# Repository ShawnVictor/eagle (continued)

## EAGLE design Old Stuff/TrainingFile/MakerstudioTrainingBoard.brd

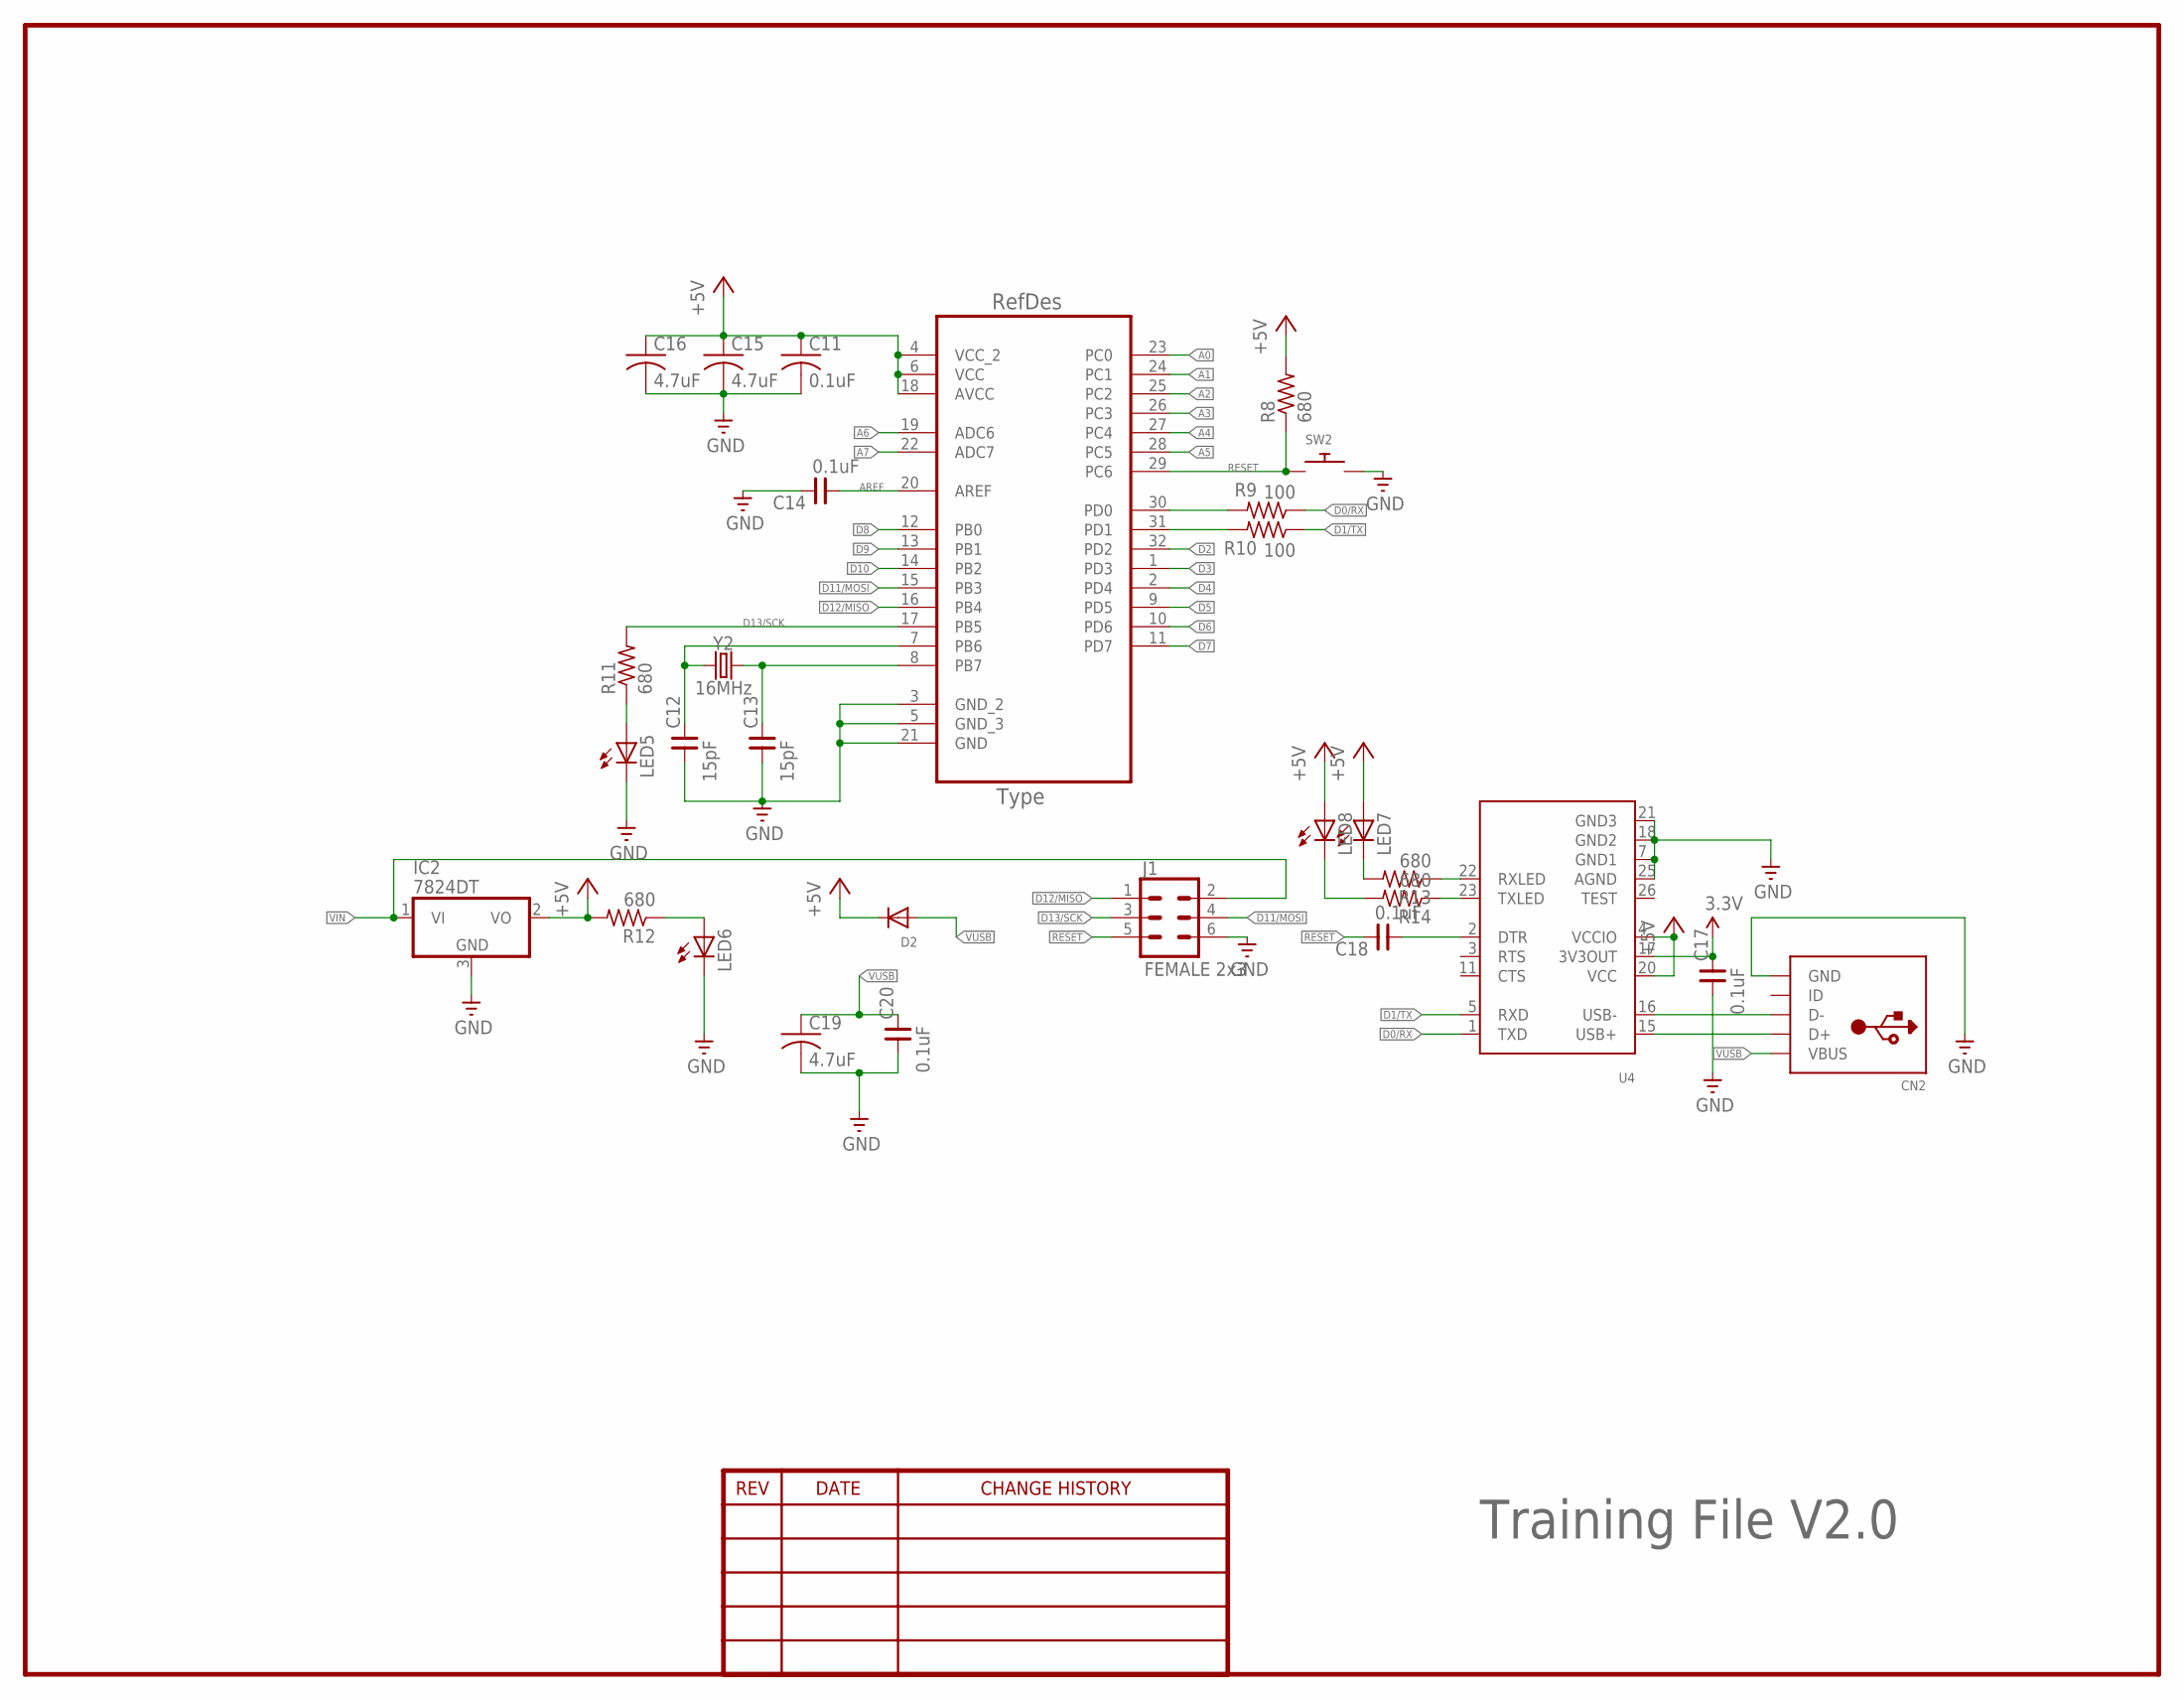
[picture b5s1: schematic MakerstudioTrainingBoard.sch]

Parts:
C11: 0.1uF; C0805
C12, C13: 15pF; 0805
C14, C17, C18, C20: 0.1uF; 0805
C15, C16, C19: 4.7uF; C0805
CN2: USBMINIB; USB-MINIB
D2: DIODESOD-123; SOD-123
IC2: 7824DT; TO252
J1: FEMALE 2x3; 2X3
LED5, LED6, LED7, LED8: LEDCHIPLED_0805; CHIPLED_0805
R8, R11, R12, R13, R14: 680; R0805
R9, R10: 100; R0805
SW2: SWITCH_PUSHBUTTONEVQ-PE; TACT_PANA-EVQ
U3: ATMEGA328P-AU; QFP80P900X900X120-32N
U4: FT232RLSSOP28; SSOP28DB
Y2: 16MHz; HC49US

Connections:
3.3V: C17.2, U4.17 (3V3OUT)
+5V: C11.1, C15.1, C16.1, D2.C, IC2.2 (VO), LED7.A, LED8.A, R8.2, R12.2, U3.4 (VCC_2), U3.6 (VCC), U3.18 (AVCC), U4.4 (VCCIO), U4.20 (VCC)
A0: U3.23 (PC0)
A1: U3.24 (PC1)
A2: U3.25 (PC2)
A3: U3.26 (PC3)
A4: U3.27 (PC4)
A5: U3.28 (PC5)
A6: U3.19 (ADC6)
A7: U3.22 (ADC7)
AREF: C14.1, U3.20 (AREF)
D0/RX: R9.1, U4.1 (TXD)
D1/TX: R10.1, U4.5 (RXD)
D2: U3.32 (PD2)
D3: U3.1 (PD3)
D4: U3.2 (PD4)
D5: U3.9 (PD5)
D6: U3.10 (PD6)
D7: U3.11 (PD7)
D8: U3.12 (PB0)
D9: U3.13 (PB1)
D10: U3.14 (PB2)
D11/MOSI: J1.4, U3.15 (PB3)
D12/MISO: J1.1, U3.16 (PB4)
D13/SCK: J1.3, R11.2, U3.17 (PB5)
GND: C11.2, C12.1, C13.1, C14.2, C15.2, C16.2, C17.1, C19.2, C20.1, CN2.GND, IC2.3 (GND), J1.6, LED5.C, LED6.C, SW2.P$2, U3.3 (GND_2), U3.5 (GND_3), U3.21 (GND), U4.7 (GND1), U4.18 (GND2), U4.21 (GND3), U4.25 (AGND)
unnamed: LED5.A, R11.1
unnamed: C13.2, U3.8 (PB7), Y2.2
unnamed: C12.2, U3.7 (PB6), Y2.1
unnamed: R9.2, U3.30 (PD0)
unnamed: R10.2, U3.31 (PD1)
unnamed: LED6.A, R12.1
unnamed: CN2.D+, U4.15 (USB+)
unnamed: CN2.D-, U4.16 (USB-)
unnamed: R13.1, U4.22 (RXLED)
unnamed: R14.1, U4.23 (TXLED)
unnamed: LED8.C, R14.2
unnamed: LED7.C, R13.2
unnamed: C18.1, U4.2 (DTR)
RESET: C18.2, J1.5, R8.1, SW2.P$1, U3.29 (PC6)
VIN: IC2.1 (VI), J1.2
VUSB: C19.1, C20.2, CN2.VBUS, D2.A

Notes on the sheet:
Training File V2.0

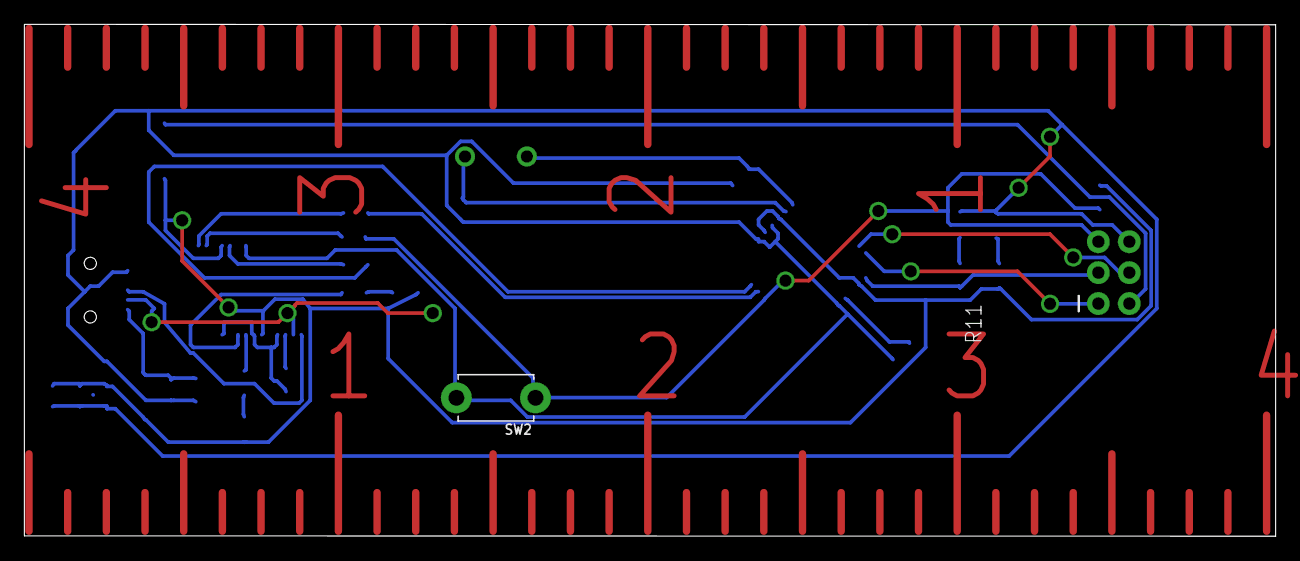
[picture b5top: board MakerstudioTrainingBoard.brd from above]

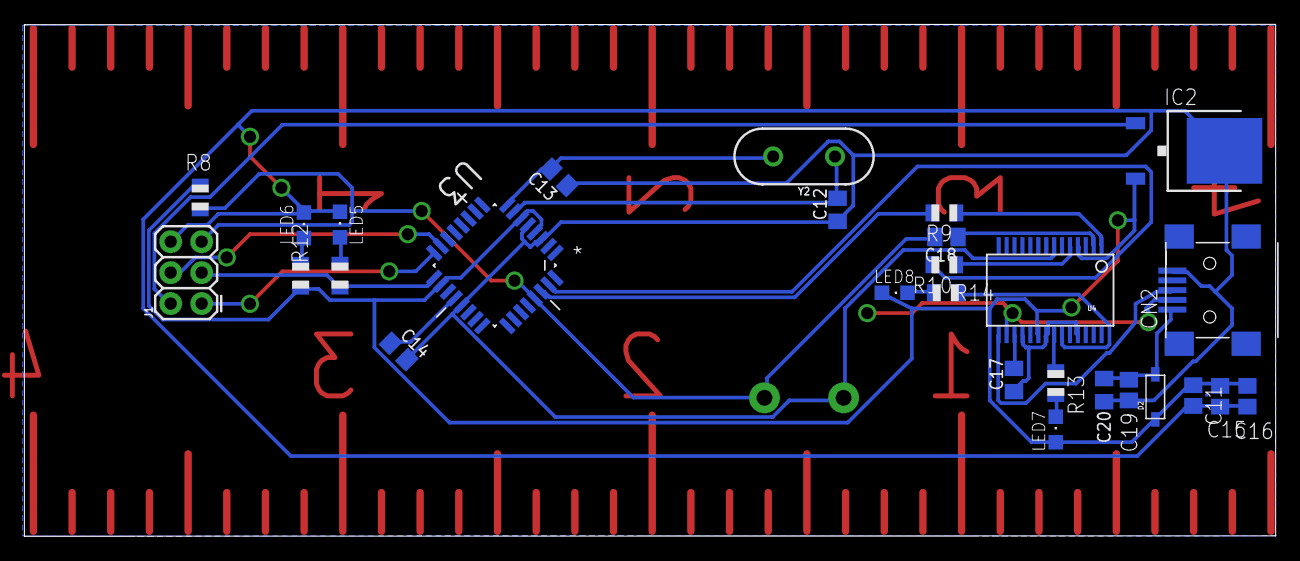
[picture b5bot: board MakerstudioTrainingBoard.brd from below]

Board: 2 copper layers, 102.7 x 42.0 mm, 29 parts (28 on the bottom side), 25 nets.

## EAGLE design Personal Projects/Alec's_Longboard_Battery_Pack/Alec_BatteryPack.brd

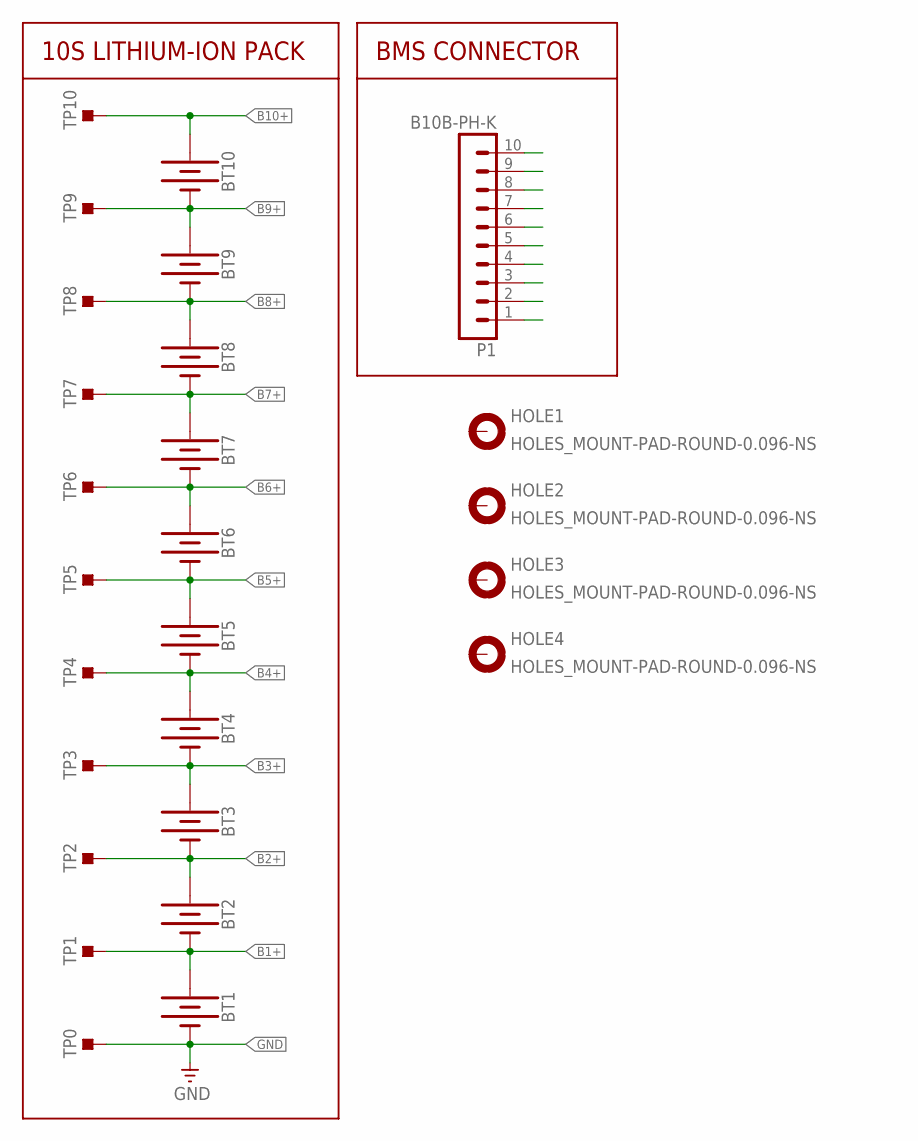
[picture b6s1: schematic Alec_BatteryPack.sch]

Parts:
BT1, BT2, BT3, BT4, BT5, BT6, BT7, BT8, BT9, BT10: BATTERY-18650; BATTERY_18650-HOLDER
HOLE1, HOLE2, HOLE3, HOLE4: HOLES_MOUNT-PAD-ROUND-0.096-NS; HOLES_096-PAD-NS
P1: B10B-PH-K
TP0, TP1, TP2, TP3, TP4, TP5, TP6, TP7, TP8, TP9, TP10: TESTPOINT_TPS-SMD-10SN; TESTPOINT_SMD-10SN

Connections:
B1+: BT1.PWR@1 (+), BT2.GND@1 (-), TP1.TP
B2+: BT2.PWR@1 (+), BT3.GND@1 (-), TP2.TP
B3+: BT3.PWR@1 (+), BT4.GND@1 (-), TP3.TP
B4+: BT4.PWR@1 (+), BT5.GND@1 (-), TP4.TP
B5+: BT5.PWR@1 (+), BT6.GND@1 (-), TP5.TP
B6+: BT6.PWR@1 (+), BT7.GND@1 (-), TP6.TP
B7+: BT7.PWR@1 (+), BT8.GND@1 (-), TP7.TP
B8+: BT8.PWR@1 (+), BT9.GND@1 (-), TP8.TP
B9+: BT9.PWR@1 (+), BT10.GND@1 (-), TP9.TP
B10+: BT10.PWR@1 (+), TP10.TP
GND: BT1.GND@1 (-), TP0.TP

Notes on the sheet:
10S LITHIUM-ION PACK
BMS CONNECTOR

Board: 2 copper layers, 26 parts (0 on the bottom side), 11 nets, no tracks yet.

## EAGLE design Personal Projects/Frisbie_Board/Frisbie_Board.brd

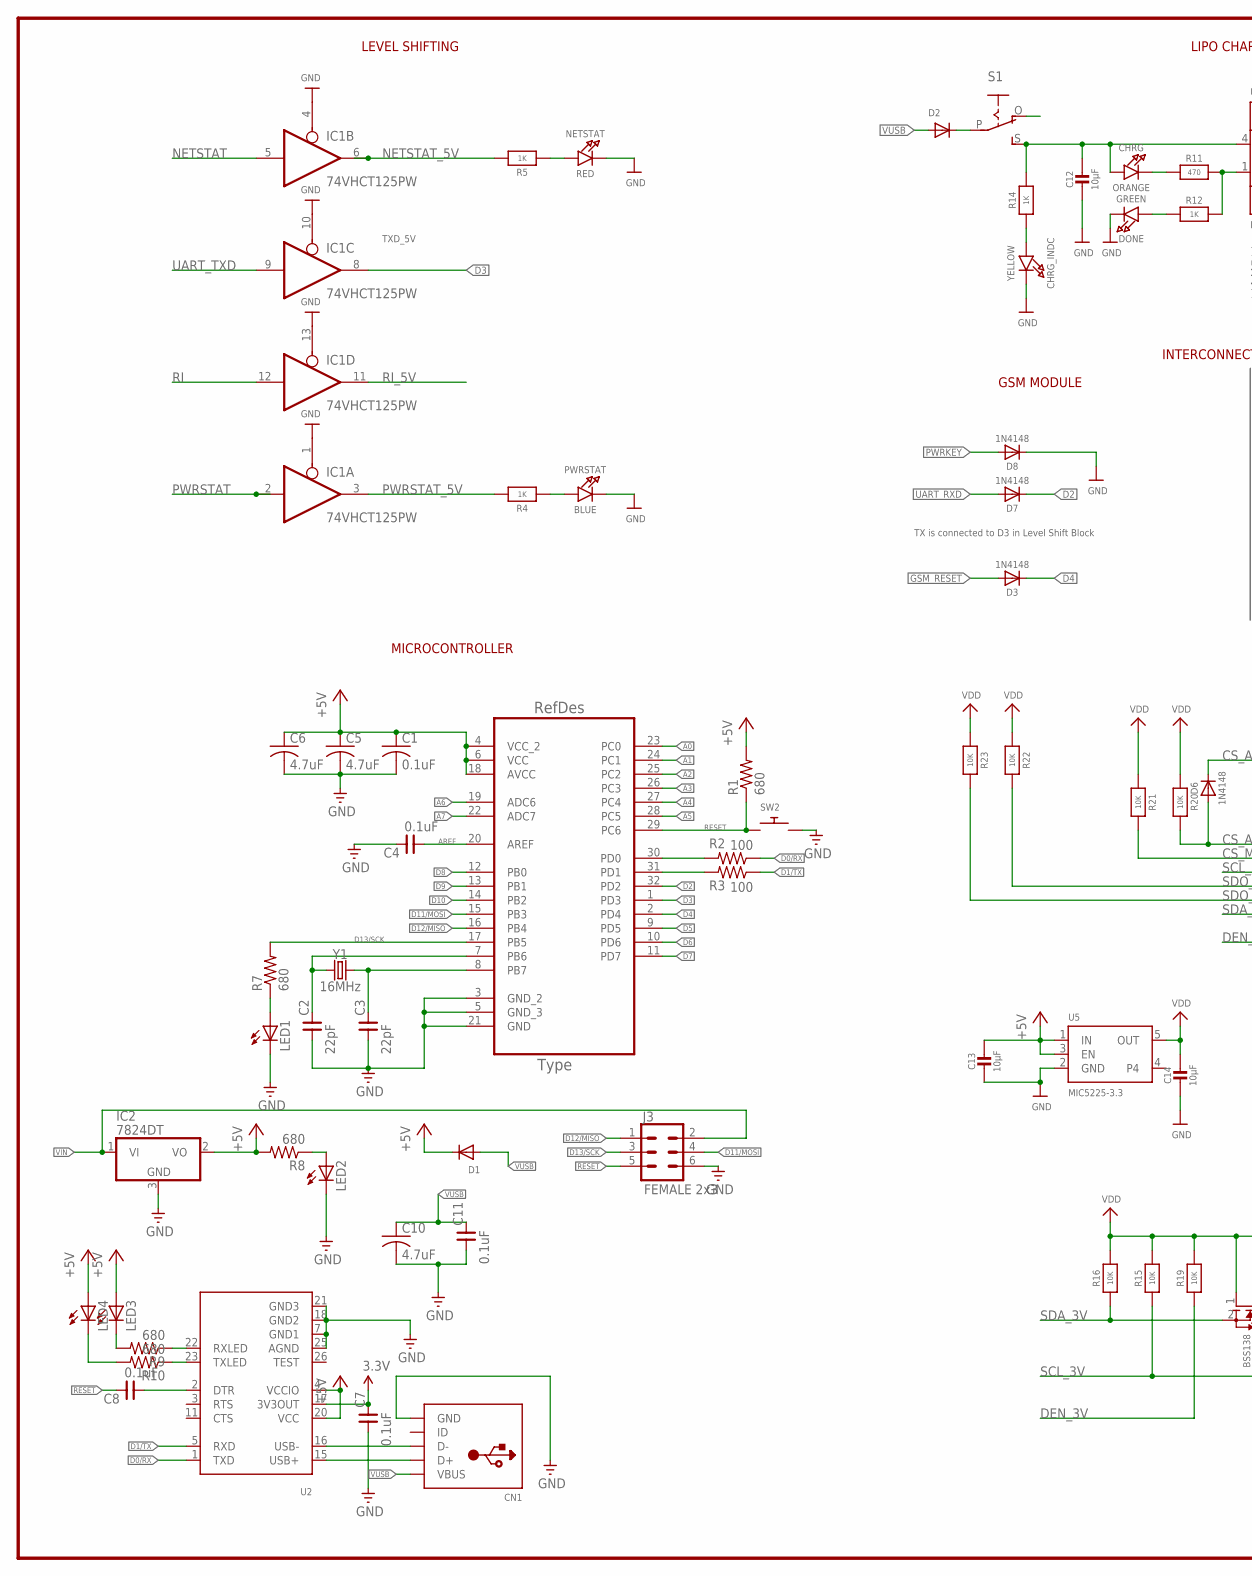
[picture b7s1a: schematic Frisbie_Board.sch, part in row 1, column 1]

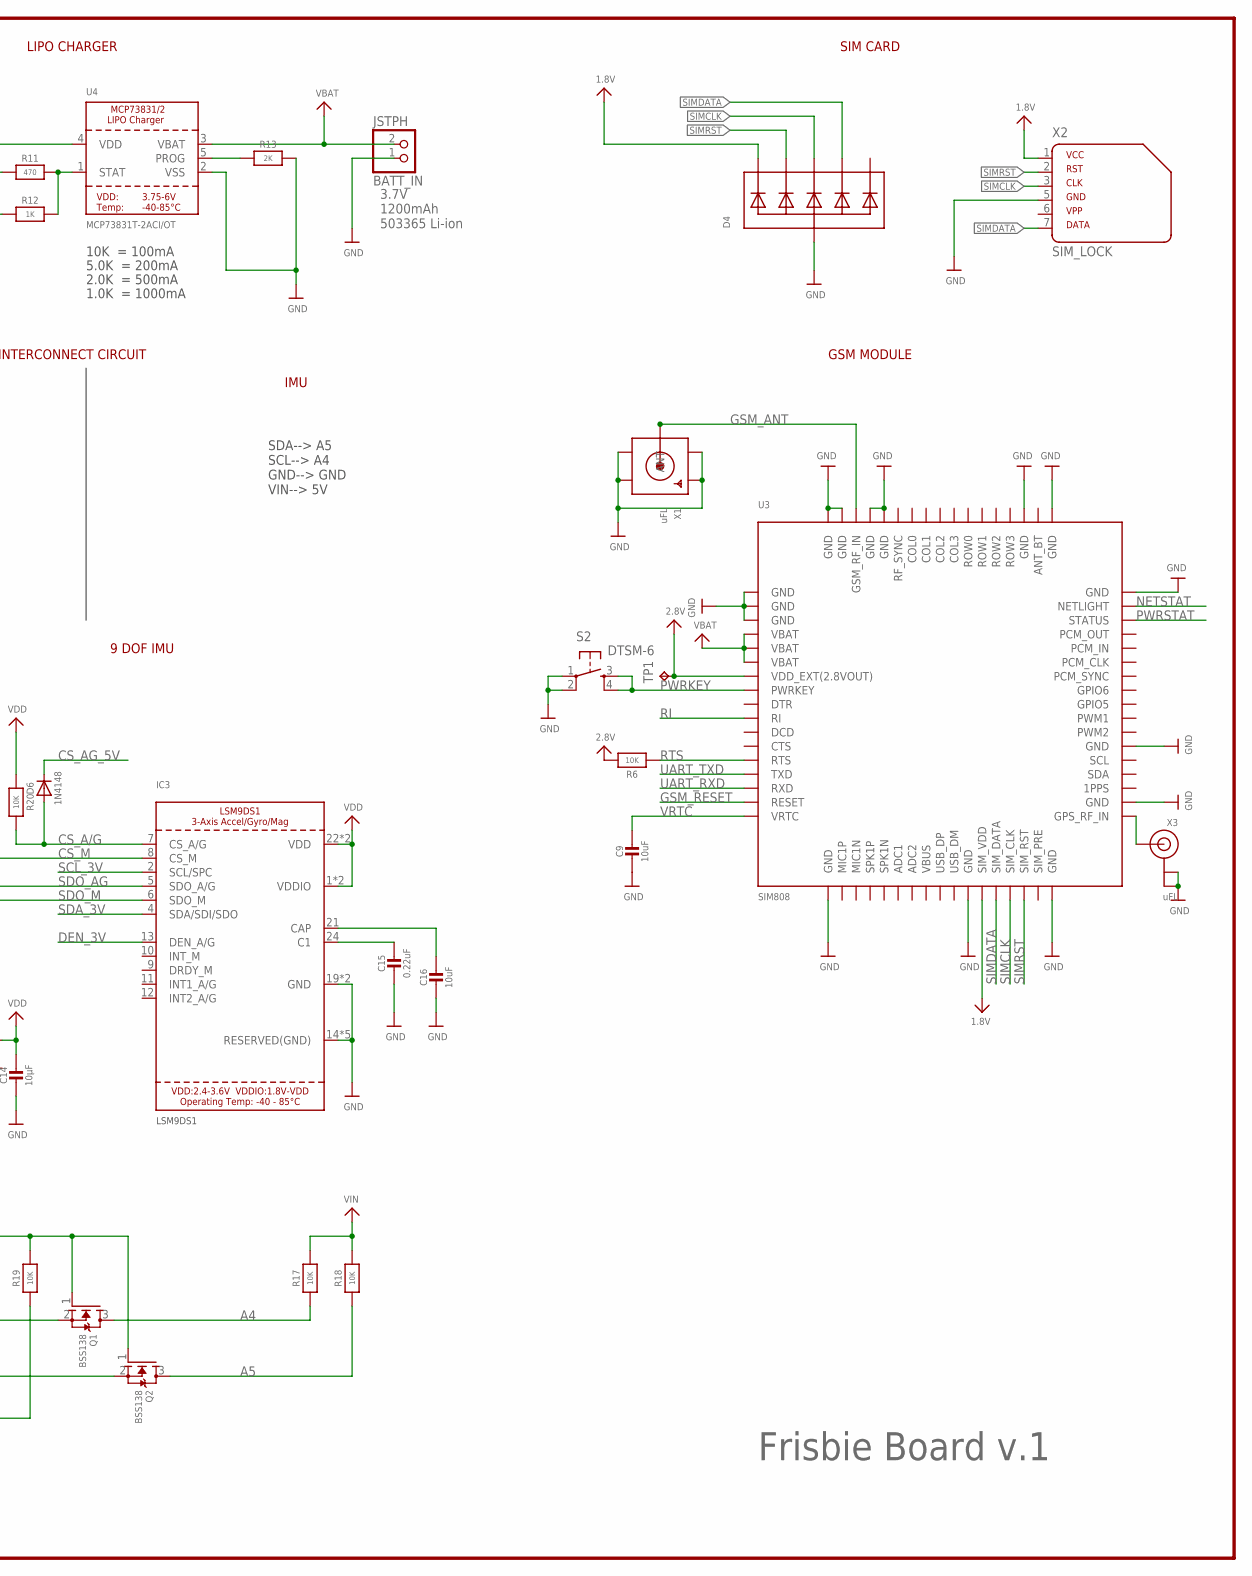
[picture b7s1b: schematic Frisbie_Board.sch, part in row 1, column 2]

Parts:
BATT_IN: JSTPH; JSTPH2
C1: 0.1uF; C0805
C2, C3: 22pF; 0805
C4, C7, C8, C11: 0.1uF; 0805
C5, C6, C10: 4.7uF; C0805
C9, C16: 10uF; 0805-NO
C12, C13, C14: 10µF; 0805-NO
C15: 0.22uF; 0805_10MGAP
CHRG: ORANGE; CHIPLED_0805_NOOUTLINE
CHRG_INDC: YELLOW; CHIPLED_0805_NOOUTLINE
CN1: USBMINIB; USB-MINIB
D1, D2: DIODESOD-123; SOD-123
D3, D6, D7, D8: 1N4148; SOD-323
D4: TVSARRAY_5LANE; SOT363
DONE: GREEN; CHIPLED_0805_NOOUTLINE
IC1: 74VHCT125PW; TSSOP14
IC2: 7824DT; TO252
IC3: LSM9DS1; LGA24_3.5X3.1MM
J3: FEMALE 2x3; 2X3
LED1, LED2, LED3, LED4: LEDCHIPLED_0805; CHIPLED_0805
NETSTAT: RED; CHIPLED_0805_NOOUTLINE
PWRSTAT: BLUE; CHIPLED_0805_NOOUTLINE
Q1, Q2: BSS138; SOT23-WIDE
R1, R7, R8, R9, R10: 680; R0805
R2, R3: 100; R0805
R4, R5, R12, R14: 1K; 0805-NO
R6, R15, R17, R18, R19, R20, R21, R23: 10K; 0805-NO
R11: 470; 0805-NO
R13: 2K; 0805-NO
R16, R22: 10K; 0805_10MGAP
S1: EG1218S; EG1218
S2: DTSM-6
SW2: SWITCH_PUSHBUTTONEVQ-PE; TACT_PANA-EVQ
TP1: TPTP11R; TP11R
U1: ATMEGA328P-AU; QFP80P900X900X120-32N
U2: FT232RLSSOP28; SSOP28DB
U3: SIM808; SIM900_SMT
U4: MCP73831T-2ACI/OT; SOT23-5
U5: MIC5225-3.3; SOT23-5
X1: uFL; SMA_EDGELAUNCH_UFL
X2: SIM_LOCK; SIM_5002
X3: uFL; U.FL
Y1: 16MHz; HC49US

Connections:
1.8V: D4.1 (C1), U3.P$29 (SIM_VDD), X2.1
2.8V: R6.2, TP1.TP, U3.P$7 (VDD_EXT(2.8VOUT))
3.3V: C7.2, U2.17 (3V3OUT)
+5V: C1.1, C5.1, C6.1, C13.1, D1.C, IC2.2 (VO), LED3.A, LED4.A, R1.2, R8.2, U1.4 (VCC_2), U1.6 (VCC), U1.18 (AVCC), U2.4 (VCCIO), U2.20 (VCC), U5.1 (IN), U5.3 (EN)
A0: U1.23 (PC0)
A1: U1.24 (PC1)
A2: U1.25 (PC2)
A3: U1.26 (PC3)
A4: Q1.3 (D), R17.1, U1.27 (PC4)
A5: Q2.3 (D), R18.1, U1.28 (PC5)
A6: U1.19 (ADC6)
A7: U1.22 (ADC7)
AREF: C4.1, U1.20 (AREF)
C1: C15.1, IC3.24 (C1)
CAP: C16.1, IC3.21 (CAP)
CS_A/G: D6.A, IC3.7 (CS_A/G), R20.2
CS_AG_5V: D6.C
CS_M: IC3.8 (CS_M), R21.2
D0/RX: R2.1, U2.1 (TXD)
D1/TX: R3.1, U2.5 (RXD)
D2: D7.C, U1.32 (PD2)
D3: IC1.8 (O), U1.1 (PD3)
D4: D3.C, U1.2 (PD4)
D5: U1.9 (PD5)
D6: U1.10 (PD6)
D7: U1.11 (PD7)
D8: U1.12 (PB0)
D9: U1.13 (PB1)
D10: U1.14 (PB2)
D11/MOSI: J3.4, U1.15 (PB3)
D12/MISO: J3.1, U1.16 (PB4)
D13/SCK: J3.3, R7.2, U1.17 (PB5)
DEN_3V: IC3.13 (DEN_A/G), R19.1
GND: BATT_IN.1, C1.2, C2.1, C3.1, C4.2, C5.2, C6.2, C7.1, C9.2, C10.2, C11.1, C12.2, C13.2, C14.2, C15.2, C16.2, CHRG_INDC.C, CN1.GND, D4.2 (A), D8.C, DONE.C, IC1.1 (OE), IC1.4 (OE), IC1.7 (GND), IC1.10 (OE), IC1.13 (OE), IC2.3 (GND), IC3.14 (RESERVED(GND)), IC3.15 (RESERVED(GND)), IC3.16 (RESERVED(GND)), IC3.17 (RESERVED(GND)), IC3.18 (RESERVED(GND)), IC3.19 (GND), IC3.20 (GND), J3.6, LED1.C, LED2.C, NETSTAT.C, PWRSTAT.C, R13.2, S2.1, S2.2, SW2.P$2, U1.3 (GND_2), U1.5 (GND_3), U1.21 (GND), U2.7 (GND1), U2.18 (GND2), U2.21 (GND3), U2.25 (AGND), U3.P$1 (GND), U3.P$2 (GND), U3.P$3 (GND), U3.P$18 (GND), U3.P$28 (GND), U3.P$34 (GND), U3.P$36 (GND), U3.P$40 (GND), U3.P$51 (GND), U3.P$52 (GND), U3.P$54 (GND), U3.P$64 (GND), U3.P$65 (GND), U3.P$67 (GND), U3.P$68 (GND), U4.2 (VSS), U5.2 (GND), X1.GND@1 (GND1), X1.GND@2 (GND2), X1.GND@3 (GND3), X1.GND@4 (GND4), X2.5 (4), X3.1 (GND), X3.2 (GND)
GSM_ANT: U3.P$66 (GSM_RF_IN), X1.P (ANT)
GSM_RESET: D3.A, U3.P$16 (RESET)
unnamed: C3.2, U1.8 (PB7), Y1.2
unnamed: C2.2, U1.7 (PB6), Y1.1
unnamed: U3.P$35 (GPS_RF_IN), X3.3 (SIGNAL)
unnamed: PWRSTAT.A, R4.1
unnamed: LED2.A, R8.1
unnamed: R2.2, U1.30 (PD0)
unnamed: R3.2, U1.31 (PD1)
unnamed: NETSTAT.A, R5.1
unnamed: CN1.D+, U2.15 (USB+)
unnamed: CN1.D-, U2.16 (USB-)
unnamed: R9.1, U2.22 (RXLED)
unnamed: R10.1, U2.23 (TXLED)
unnamed: LED3.C, R9.2
unnamed: LED4.C, R10.2
unnamed: C8.1, U2.2 (DTR)
unnamed: CHRG.C, R11.1
unnamed: R11.2, R12.2, U4.1 (STAT)
unnamed: R13.1, U4.5 (PROG)
unnamed: DONE.A, R12.1
unnamed: C12.1, CHRG.A, R14.2, S1.S, U4.4 (VDD)
unnamed: D2.C, S1.P
unnamed: CHRG_INDC.A, R14.1
unnamed: LED1.A, R7.1
NETSTAT: IC1.5 (I), U3.P$50 (NETLIGHT)
NETSTAT_5V: IC1.6 (O), R5.2
PWRKEY: D8.A, S2.3, S2.4, U3.P$8 (PWRKEY)
PWRSTAT: IC1.2 (I), U3.P$49 (STATUS)
PWRSTAT_5V: IC1.3 (O), R4.2
RESET: C8.2, J3.5, R1.1, SW2.P$1, U1.29 (PC6)
RI: IC1.12 (I), U3.P$10 (RI)
RI_5V: IC1.11 (O)
RTS: R6.1, U3.P$13 (RTS)
SCL_3V: IC3.2 (SCL/SPC), Q2.2 (S), R15.1
SDA_3V: IC3.4 (SDA/SDI/SDO), Q1.2 (S), R16.1
SDO_AG: IC3.5 (SDO_A/G), R22.2
SDO_M: IC3.6 (SDO_M), R23.2
SIMCLK: D4.4 (C3), U3.P$31 (SIM_CLK), X2.3
SIMDATA: D4.5 (C4), U3.P$30 (SIM_DATA), X2.7 (6)
SIMRST: D4.3 (C2), U3.P$32 (SIM_RST), X2.2
UART_RXD: D7.A, U3.P$15 (RXD)
UART_TXD: IC1.9 (I), U3.P$14 (TXD)
VBAT: BATT_IN.2, U3.P$4 (VBAT), U3.P$5 (VBAT), U3.P$6 (VBAT), U4.3 (VBAT)
VCC: IC1.14 (VCC)
VDD: C14.1, IC3.1 (VDDIO), IC3.3 (VDDIO), IC3.22 (VDD), IC3.23 (VDD), Q1.1 (G), Q2.1 (G), R15.2, R16.2, R19.2, R20.1, R21.1, R22.1, R23.1, U5.5 (OUT)
VIN: IC2.1 (VI), J3.2, R17.2, R18.2
VRTC: C9.1, U3.P$17 (VRTC)
VUSB: C10.1, C11.2, CN1.VBUS, D1.A, D2.A, U3.P$25 (VBUS)

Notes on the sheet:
LEVEL SHIFTING
10K = 100mA
5.0K = 200mA
2.0K = 500mA
1.0K = 1000mA
LIPO CHARGER
3.7V 1200mAh 503365 Li-ion
INTERCONNECT CIRCUIT
TXD_5V
TX is connected to D3 in Level Shift Block
SIM CARD
GSM MODULE
MICROCONTROLLER
9 DOF IMU
SDA--> A5 SCL--> A4 GND--> GND VIN--> 5V
IMU
Frisbie Board v.1

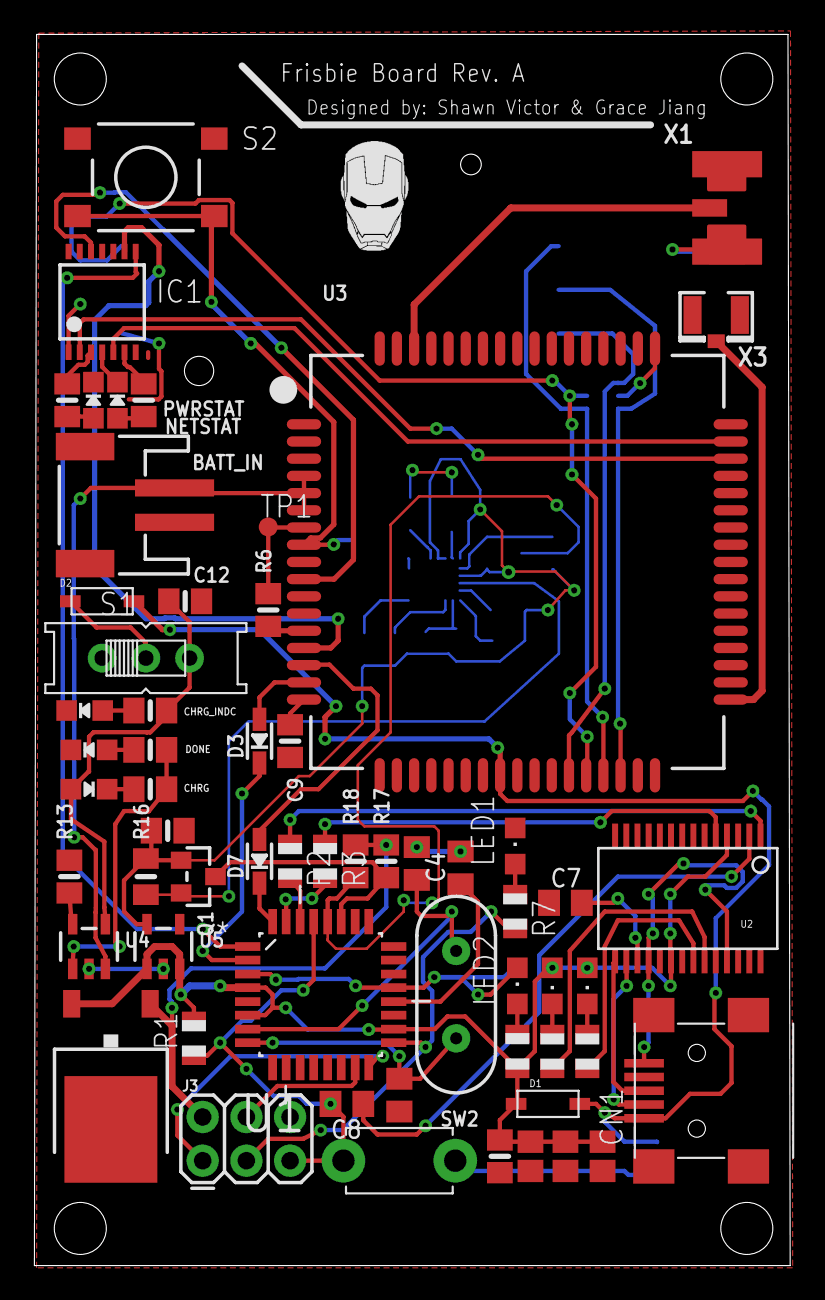
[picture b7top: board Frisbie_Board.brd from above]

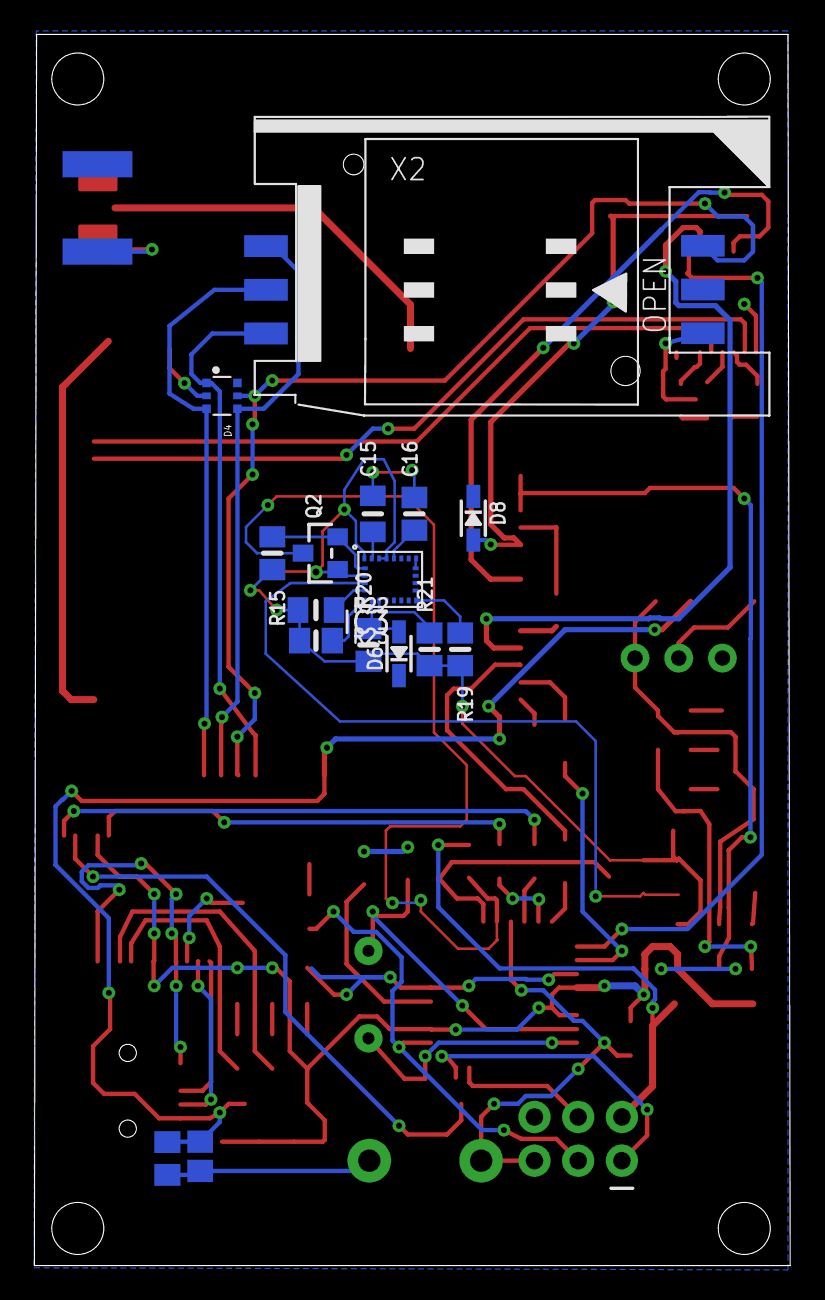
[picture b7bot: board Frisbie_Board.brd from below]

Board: 2 copper layers, 43.9 x 71.6 mm, 76 parts (16 on the bottom side), 68 nets.
